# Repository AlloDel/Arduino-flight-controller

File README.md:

# Arduino-flight-controller
A simple flight controller using arduino for a quadcopter designed for a group of aerospace engineering students in KNUST

PDFs and images of schematic and 3d renders are listed in /ArduinoFC_v.1.1 pics and docs directory

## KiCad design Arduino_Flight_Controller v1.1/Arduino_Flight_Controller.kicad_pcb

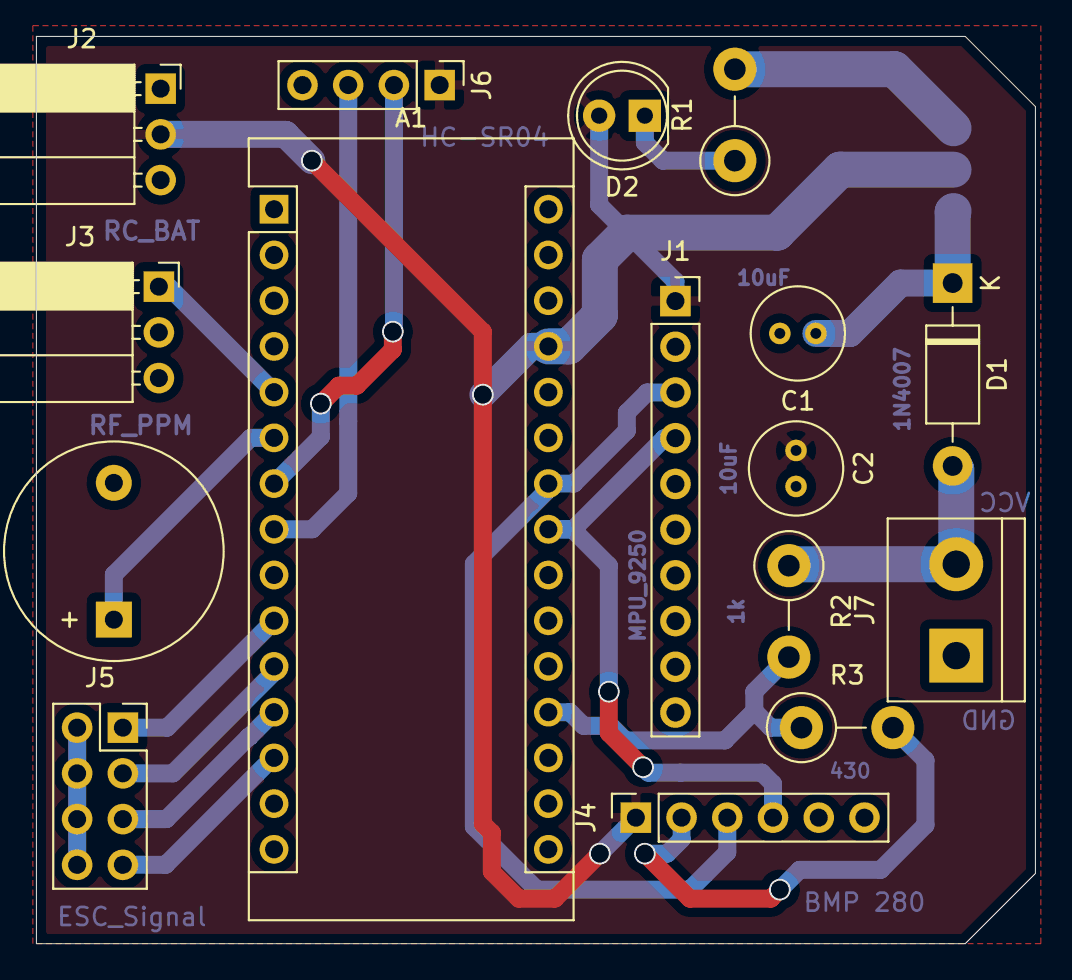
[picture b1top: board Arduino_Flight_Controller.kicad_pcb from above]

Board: 2 copper layers, 55.5 x 50.4 mm, 17 parts (1 on the bottom side), 16 nets.

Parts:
A1: Arduino_Nano_v3.x; Arduino_Nano
BZ1: Buzzer; Buzzer_12x9.5RM7.6
C1, C2: 10uF; C_Radial_D5.0mm_H7.0mm_P2.00mm
D1: 1N4007; D_DO-41_SOD81_P10.16mm_Horizontal
D2: LED_Small; LED_D5.0mm_Clear
J1: MPU_9250; PinSocket_1x10_P2.54mm_Vertical
J2: RC_BAT; PinSocket_1x03_P2.54mm_Horizontal
J3: RF_PPM; PinSocket_1x03_P2.54mm_Horizontal
J4: BMP_280; PinSocket_1x06_P2.54mm_Vertical
J5: ESC_Signal; PinSocket_2x04_P2.54mm_Vertical
J6: HC-SRO4; PinHeader_1x04_P2.54mm_Vertical
J7: Screw_Terminal_01x02; TerminalBlock_bornier-2_P5.08mm
R1, R3: 430; R_Axial_DIN0411_L9.9mm_D3.6mm_P5.08mm_Vertical
R2: 1k; R_Axial_DIN0411_L9.9mm_D3.6mm_P5.08mm_Vertical
U1: AMS1117-5.0; SOT-223-3_TabPin2

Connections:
+5V: A1.27, C2.1, D2.2, J1.1, J2.2, J4.1, J6.1, U1.2
/BARO_SCL: A1.24, J1.3, J4.3
/BARO_SDA: A1.23, J1.4, J4.4
/BATT_VOLT: A1.19, R2.2, R3.1
/BUZZER: A1.6, BZ1.1
/ECHO: A1.8, J6.3
/ESC_1(RF): A1.10, J5.1
/ESC_2(RR): A1.11, J5.3
/ESC_3(LR): A1.12, J5.5
/ESC_4(LF): A1.13, J5.7
/PPM: A1.5, J3.1
/TRIG: A1.7, J6.2
GND: A1.4, A1.29, BZ1.2, C1.2, C2.2, J1.2, J2.3, J4.2, J5.2, J5.4, J5.6, J5.8, J6.4, J7.1, R1.2, R3.2, U1.1
unnamed: C1.1, D1.1, U1.3
unnamed: D2.1, R1.1
VCC: D1.2, J7.2, R2.1
